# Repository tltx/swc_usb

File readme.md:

SWC USB Adapter
===============

SWC USB Adapter is a peripheral for the Super Wild Card backup unit that makes it USB compatible.

Features
--------
* Connect a Super Wild Card via USB to a modern computer that does not have a parallel port.
* Compatible with most operating systems. The program is writen in Python and the adapter uses the USB CDC driver that is built into most modern operating systems.
* Transfer speed on par with parallel port transfer.
* No need for a thick parallel port cable.
* More convenient than floppies or a USB floppy emulator.
* The hardware parts are widely available and not too hard to assemble.
* Program auto detects the adapter, no need to specify the port.
* It is a open hardware and software project.

Usage example
-------------

To transfer a ROM file to the Super Wild Card:

`swc_usb.py send-rom --hirom <file>`

To fetch a SRAM dump:

`swc_usb.py fetch-sram <file>`

Questions and answers
----------------------
Q: Why not just use any USB to parallel adapter?

A: It won't work, almost all of them are for printers only, and if you find one that truly emulates a parallel port the latency of USB will make the transfers really slow.

Q: Do I need to surface mount solder and have a PCB manufactured?

A: You should be able to use any Atmega32u4 breakout board and solder wires from it to a male D-Sub 25 connector. That project hardware is basically the same thing but in a nicer form factor.

Q: How do I compile the firmware?

A: swc_usb.hex is a compiled firmware ready to be loaded onto the controller. If you want to compile it yourself, set up a AVR tool chain and run `make all` in the firmware directory.

Q: Does it have all the swc transfer features that Ucon64 has?

A: No, It can send ROM files, send SRAM, fetch SRAM. If there is interest in some other feature I might add it.

Q: Which variants of the Super Wild Card is supported?

A: I think it works on all but I have tested it on: Super Magicom (MS-3201), Super Wild Card (SMS3201), Super Wild Card DX (SWC3201)

Atmega32u4 pin mapping to the D-Sub
-----------------------------------

| Atmega32u4 | D-Sub |
|------------|-------|
| PB3        | 15    |
| PB4        | 13    |
| PB5        | 12    |
| PB6        | 10    |
| PB7        | 11    |
| PD0        | 2     |
| PD1        | 3     |
| PD2        | 4     |
| PD3        | 5     |
| PD4        | 6     |
| PD5        | 7     |
| PD6        | 8     |
| PD7        | 9     |
| PF4        | 1     |
| PF5        | 14    |
| PF6        | 16    |
| PF7        | 17    |
| GND        | 25    |

Thanks
------
This project would probably not have been made without the awesome [LUFA](http://www.fourwalledcubicle.com/LUFA.php) library. [Ucon64](http://ucon64.sourceforge.net/) have been a great source of information on how to communicate with the SWC and a starting point for code.

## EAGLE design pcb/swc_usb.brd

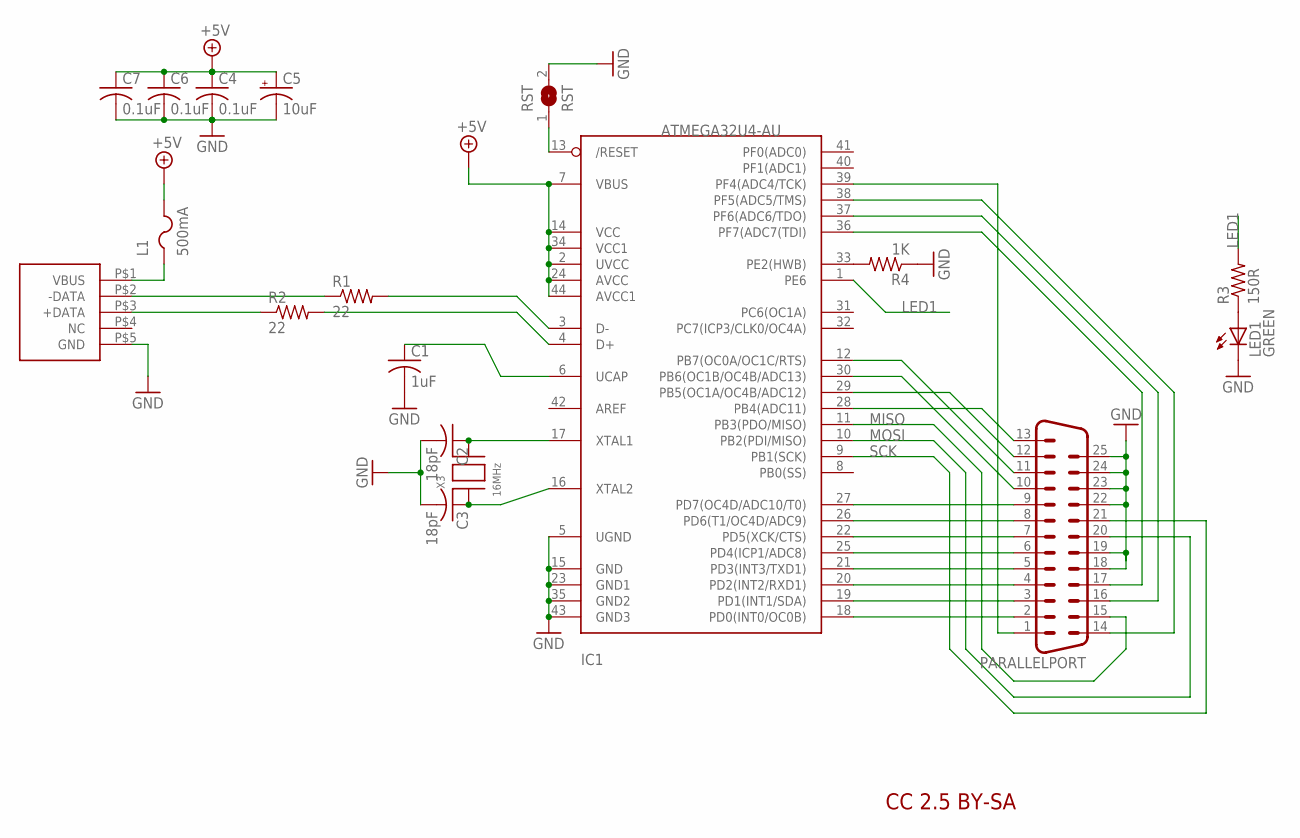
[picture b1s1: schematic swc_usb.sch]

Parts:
C1: 1uF; C0805K; MPN 0805B104K500CT
C2, C3: 18pF; C0805K; MPN 0805N180J500CT
C4, C6, C7: 0.1uF; C0805K; MPN 0805B104K500CT
C5: 10uF; A/3216-18R; MPN 1206B106K160CT
IC1: ATMEGA32U4-AU; TQFP44; MPN ATMEGA32U4-AU
L1: 500mA; R1206; MPN 1206L050YR.
LED1: GREEN; LED5MM; MPN SSL-LX5093XAC
PARALLELPORT: M25D; MPN SDB25PTD
R1, R2: 22; R0805; MPN WCR0805-22RFI
R3: 150R; R0805; MPN WCR0805-150RFI
R4: 1K; R0805; MPN RC0805FR-071KL
RST: RST; SJ
U$1: MICRO_USB_MID; MPN 47491-0001
X3: 16MHz; NX5032; MPN X1G0044510002 SG5032CAN 16 MHZ TJGA

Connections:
+5V: C4.1, C5.+, C6.1, C7.1, IC1.2 (UVCC), IC1.7 (VBUS), IC1.14 (VCC), IC1.24 (AVCC), IC1.34 (VCC1), IC1.44 (AVCC1), L1.2
GND: C1.2, C2.2, C3.2, C4.2, C5.-, C6.2, C7.2, IC1.5 (UGND), IC1.15 (GND), IC1.23 (GND1), IC1.35 (GND2), IC1.43 (GND3), LED1.K (C), PARALLELPORT.18, PARALLELPORT.19, PARALLELPORT.22, PARALLELPORT.23, PARALLELPORT.24, PARALLELPORT.25, R4.1, RST.2, U$1.P$5 (GND)
LED1: IC1.1 (PE6), R3.2
MISO: IC1.11 (PB3(PDO/MISO)), PARALLELPORT.15
MOSI: IC1.10 (PB2(PDI/MISO)), PARALLELPORT.20
unnamed: LED1.A, R3.1
unnamed: R2.1, U$1.P$3 (+DATA)
unnamed: IC1.3 (D-), R1.2
unnamed: IC1.4 (D+), R2.2
unnamed: R1.1, U$1.P$2 (-DATA)
unnamed: IC1.18 (PD0(INT0/OC0B)), PARALLELPORT.2
unnamed: IC1.19 (PD1(INT1/SDA)), PARALLELPORT.3
unnamed: C2.1, IC1.17 (XTAL1), X3.P$2
unnamed: C3.1, IC1.16 (XTAL2), X3.P$1
unnamed: C1.1, IC1.6 (UCAP)
unnamed: IC1.20 (PD2(INT2/RXD1)), PARALLELPORT.4
unnamed: IC1.21 (PD3(INT3/TXD1)), PARALLELPORT.5
unnamed: IC1.25 (PD4(ICP1/ADC8)), PARALLELPORT.6
unnamed: IC1.22 (PD5(XCK/CTS)), PARALLELPORT.7
unnamed: IC1.26 (PD6(T1/OC4D/ADC9)), PARALLELPORT.8
unnamed: IC1.27 (PD7(OC4D/ADC10/T0)), PARALLELPORT.9
unnamed: IC1.28 (PB4(ADC11)), PARALLELPORT.13
unnamed: IC1.29 (PB5(OC1A/OC4B/ADC12)), PARALLELPORT.12
unnamed: IC1.30 (PB6(OC1B/OC4B/ADC13)), PARALLELPORT.10
unnamed: IC1.12 (PB7(OC0A/OC1C/RTS)), PARALLELPORT.11
unnamed: IC1.39 (PF4(ADC4/TCK)), PARALLELPORT.1
unnamed: IC1.33 (PE2(HWB)), R4.2
unnamed: IC1.36 (PF7(ADC7(TDI)), PARALLELPORT.17
unnamed: IC1.37 (PF6(ADC6/TDO)), PARALLELPORT.16
unnamed: IC1.38 (PF5(ADC5/TMS)), PARALLELPORT.14
RST: IC1.13 (/RESET), RST.1
SCK: IC1.9 (PB1(SCK)), PARALLELPORT.21
VBUS: L1.1, U$1.P$1 (VBUS)

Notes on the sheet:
CC 2.5 BY-SA

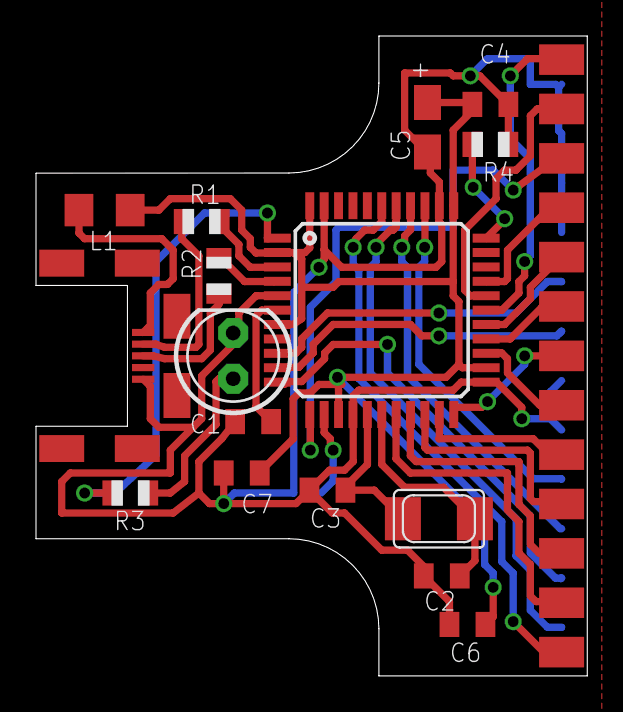
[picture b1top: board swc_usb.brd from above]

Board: 2 copper layers, 30.6 x 35.5 mm, 18 parts (1 on the bottom side), 33 nets.

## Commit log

2016-06-24 Replace tab indentation with spaces
2017-02-11 Add HiROM/LoROM and SRAM size auto detection
2019-05-01 Done some testing
